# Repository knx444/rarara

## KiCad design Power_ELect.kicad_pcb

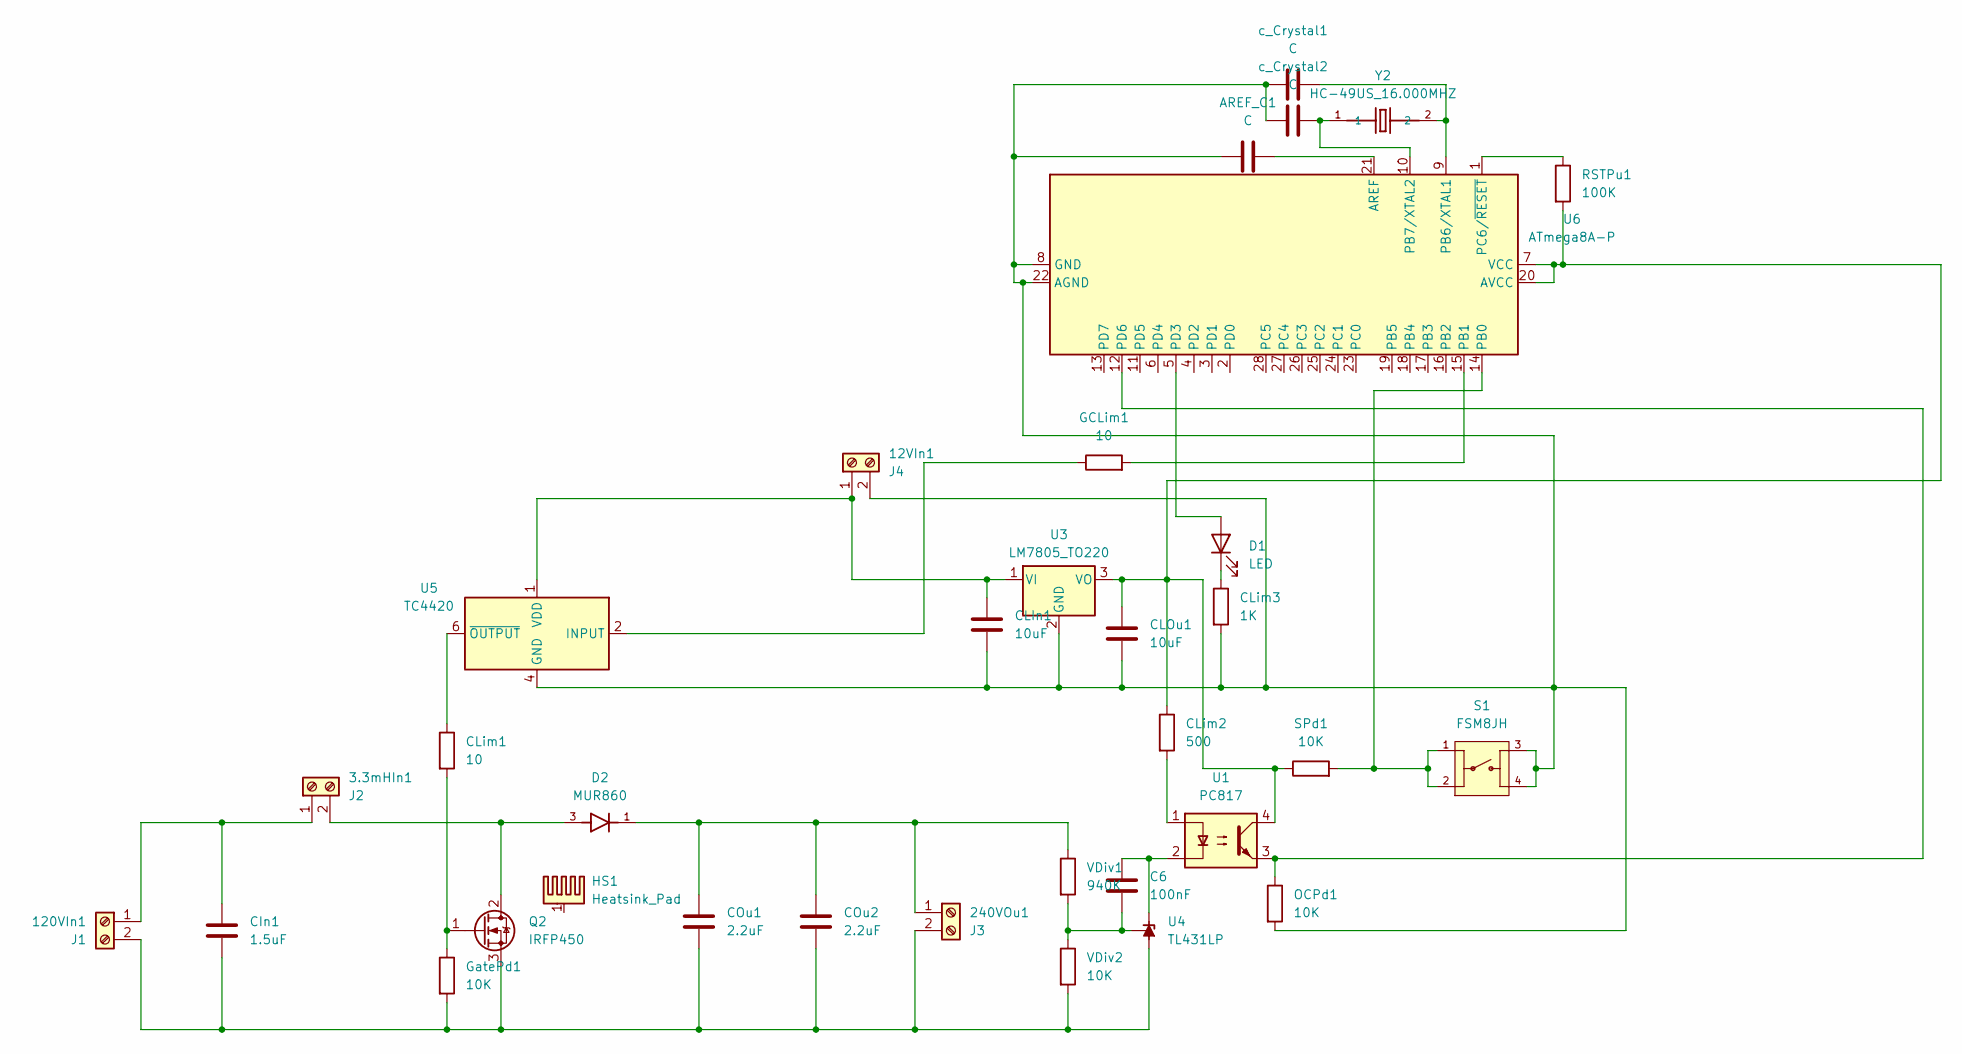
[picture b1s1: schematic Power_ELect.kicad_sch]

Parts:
3.3mHIn1: J2; TerminalBlock_MetzConnect_Type094_RT03502HBLU_1x02_P5.00mm_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
12VIn1: J4; TerminalBlock_MetzConnect_Type094_RT03502HBLU_1x02_P5.00mm_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
120VIn1: J1; TerminalBlock_MetzConnect_Type094_RT03502HBLU_1x02_P5.00mm_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
240VOu1: J3; TerminalBlock_MetzConnect_Type094_RT03502HBLU_1x02_P5.00mm_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
AREF_C1: C; C_Radial_D5.0mm_H11.0mm_P2.00mm
C6: 100nF; C_Disc_D10.0mm_W2.5mm_P5.00mm
CIn1: 1.5uF; C_Rect_L15mm_W10mm_P16.00mm_MKT
CLIn1: 10uF; C_Radial_D6.3mm_H5.0mm_P2.50mm
CLOu1: 10uF; C_Radial_D6.3mm_H5.0mm_P2.50mm
CLim1: 10; R_Axial_DIN0411_L9.9mm_D3.6mm_P12.70mm_Horizontal
CLim2: 500; R_Axial_DIN0309_L9.0mm_D3.2mm_P12.70mm_Horizontal
CLim3: 1K; R_Axial_DIN0411_L9.9mm_D3.6mm_P12.70mm_Horizontal
COu1, COu2: 2.2uF; C_Rect_L22.0mm_W10.0mm_P20.00mm_MKS4
D1: LED; LED_D5.0mm
D2: MUR860; TO508P1050X476X2020-2; PARTREV G2103
GCLim1: 10; R_Axial_DIN0411_L9.9mm_D3.6mm_P12.70mm_Horizontal
GatePd1: 10K; R_Axial_DIN0411_L9.9mm_D3.6mm_P12.70mm_Horizontal
HS1: Heatsink_Pad; Heatsink_45x15mm_2xFixation3mm
OCPd1: 10K; R_Axial_DIN0309_L9.0mm_D3.2mm_P12.70mm_Horizontal
Q2: IRFP450; TO-247-3_Vertical
RSTPu1: 100K; R_Axial_DIN0411_L9.9mm_D3.6mm_P12.70mm_Horizontal
S1: FSM8JH; SW_FSM8JH; PARTREV C10
SPd1: 10K; R_Axial_DIN0309_L9.0mm_D3.2mm_P12.70mm_Horizontal
U1: PC817; DIP-4_W7.62mm
U3: LM7805_TO220; TO-220-3_Vertical
U4: TL431LP; TO-92_Inline
U5: TC4420; DIP-8_W7.62mm
U6: ATmega8A-P; DIP-28_W7.62mm
VDiv1: 940K; R_Axial_DIN0309_L9.0mm_D3.2mm_P12.70mm_Horizontal
VDiv2: 10K; R_Axial_DIN0309_L9.0mm_D3.2mm_P12.70mm_Horizontal
Y2: HC-49US_16.000MHZ; XTAL_HC-49US-16.000MHZ
c_Crystal1, c_Crystal2: C; C_Disc_D4.3mm_W1.9mm_P5.00mm

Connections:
unnamed: 3.3mHIn1.2, D2.3, Q2.2 (D)
unnamed: 12VIn1.1, CLIn1.1, U3.1 (VI), U5.1 (VDD), U5.8 (VDD)
unnamed: 12VIn1.2, AREF_C1.1, CLIn1.2, CLOu1.2, CLim3.2, OCPd1.2, S1.3, S1.4, U3.2 (GND), U5.4 (GND), U5.5 (GND), U6.8 (GND), U6.22 (AGND), c_Crystal1.1, c_Crystal2.1
unnamed: 3.3mHIn1.1, 120VIn1.1, CIn1.1
unnamed: 120VIn1.2, 240VOu1.2, CIn1.2, COu1.2, COu2.2, GatePd1.2, Q2.3 (S), U4.2 (A), VDiv2.2
unnamed: 240VOu1.1, COu1.1, COu2.1, D2.1, VDiv1.1
unnamed: CLim1.1, U5.6 (~OUTPUT), U5.7 (~OUTPUT)
unnamed: CLim2.2, U1.1
unnamed: D1.2 (A), U6.5 (PD3)
unnamed: CLim3.1, D1.1 (K)
unnamed: CLim1.2, GatePd1.1, Q2.1 (G)
unnamed: CLOu1.1, CLim2.1, RSTPu1.2, SPd1.1, U1.4, U3.3 (VO), U6.7 (VCC), U6.20 (AVCC)
unnamed: C6.1, U1.2, U4.3 (K)
unnamed: C6.2, U4.1 (REF), VDiv1.2, VDiv2.1
unnamed: GCLim1.1, U5.2 (INPUT)
unnamed: AREF_C1.2, U6.21 (AREF)
unnamed: S1.1, S1.2, SPd1.2, U6.14 (PB0)
unnamed: GCLim1.2, U6.15 (PB1)
unnamed: U6.9 (PB6/XTAL1), Y2.2, c_Crystal1.2
unnamed: U6.10 (PB7/XTAL2), Y2.1, c_Crystal2.2
unnamed: RSTPu1.1, U6.1 (PC6/~RESET)
unnamed: OCPd1.1, U1.3, U6.12 (PD6)

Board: 2 copper layers, 34 parts (0 on the bottom side), 22 nets, no tracks yet.
